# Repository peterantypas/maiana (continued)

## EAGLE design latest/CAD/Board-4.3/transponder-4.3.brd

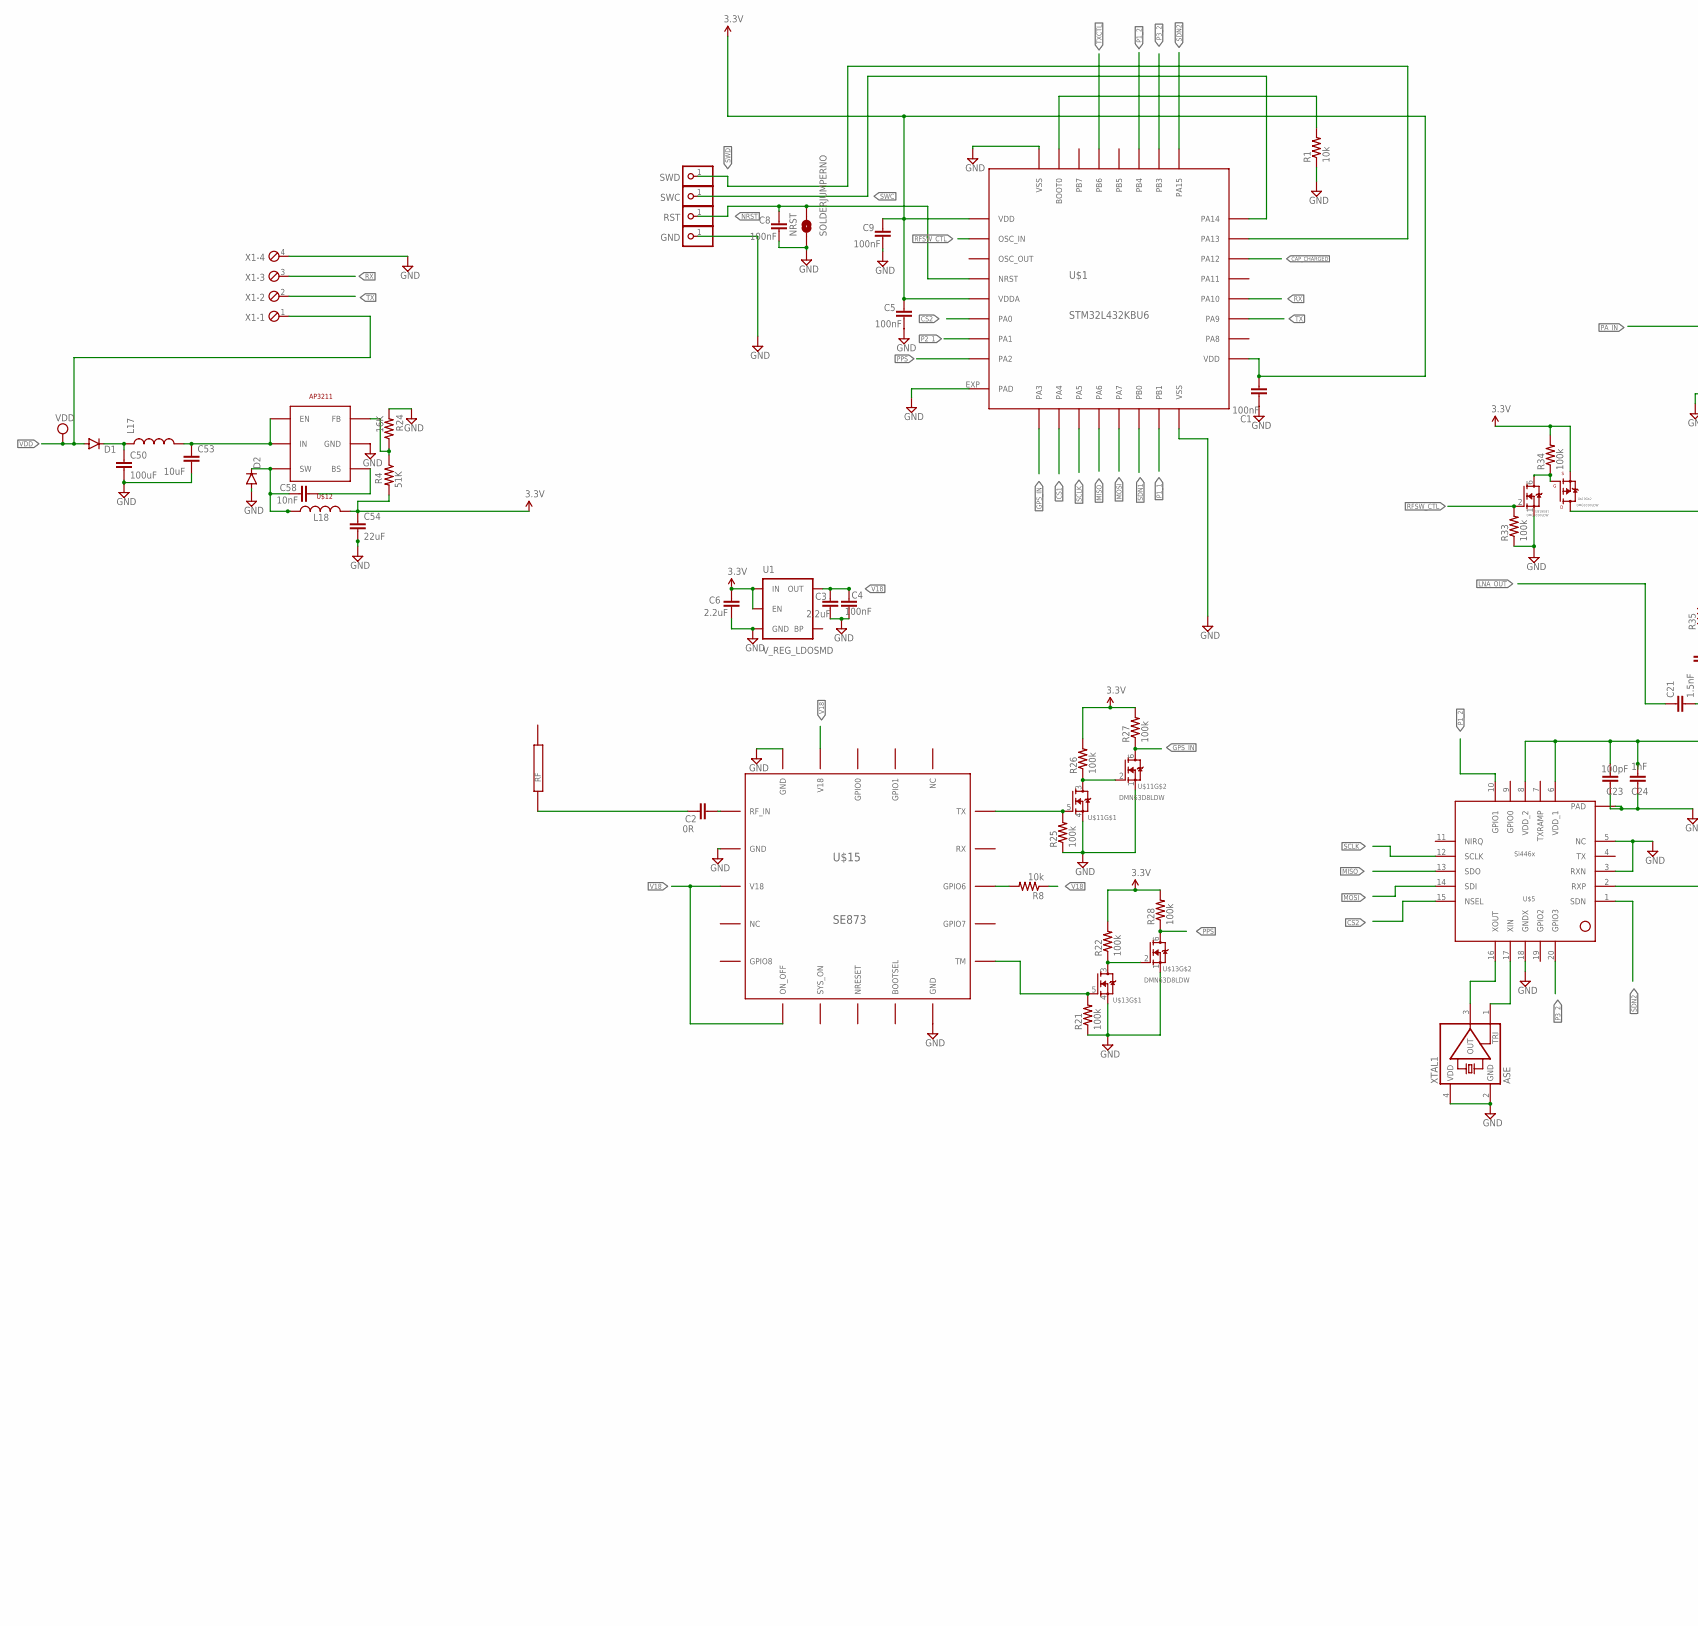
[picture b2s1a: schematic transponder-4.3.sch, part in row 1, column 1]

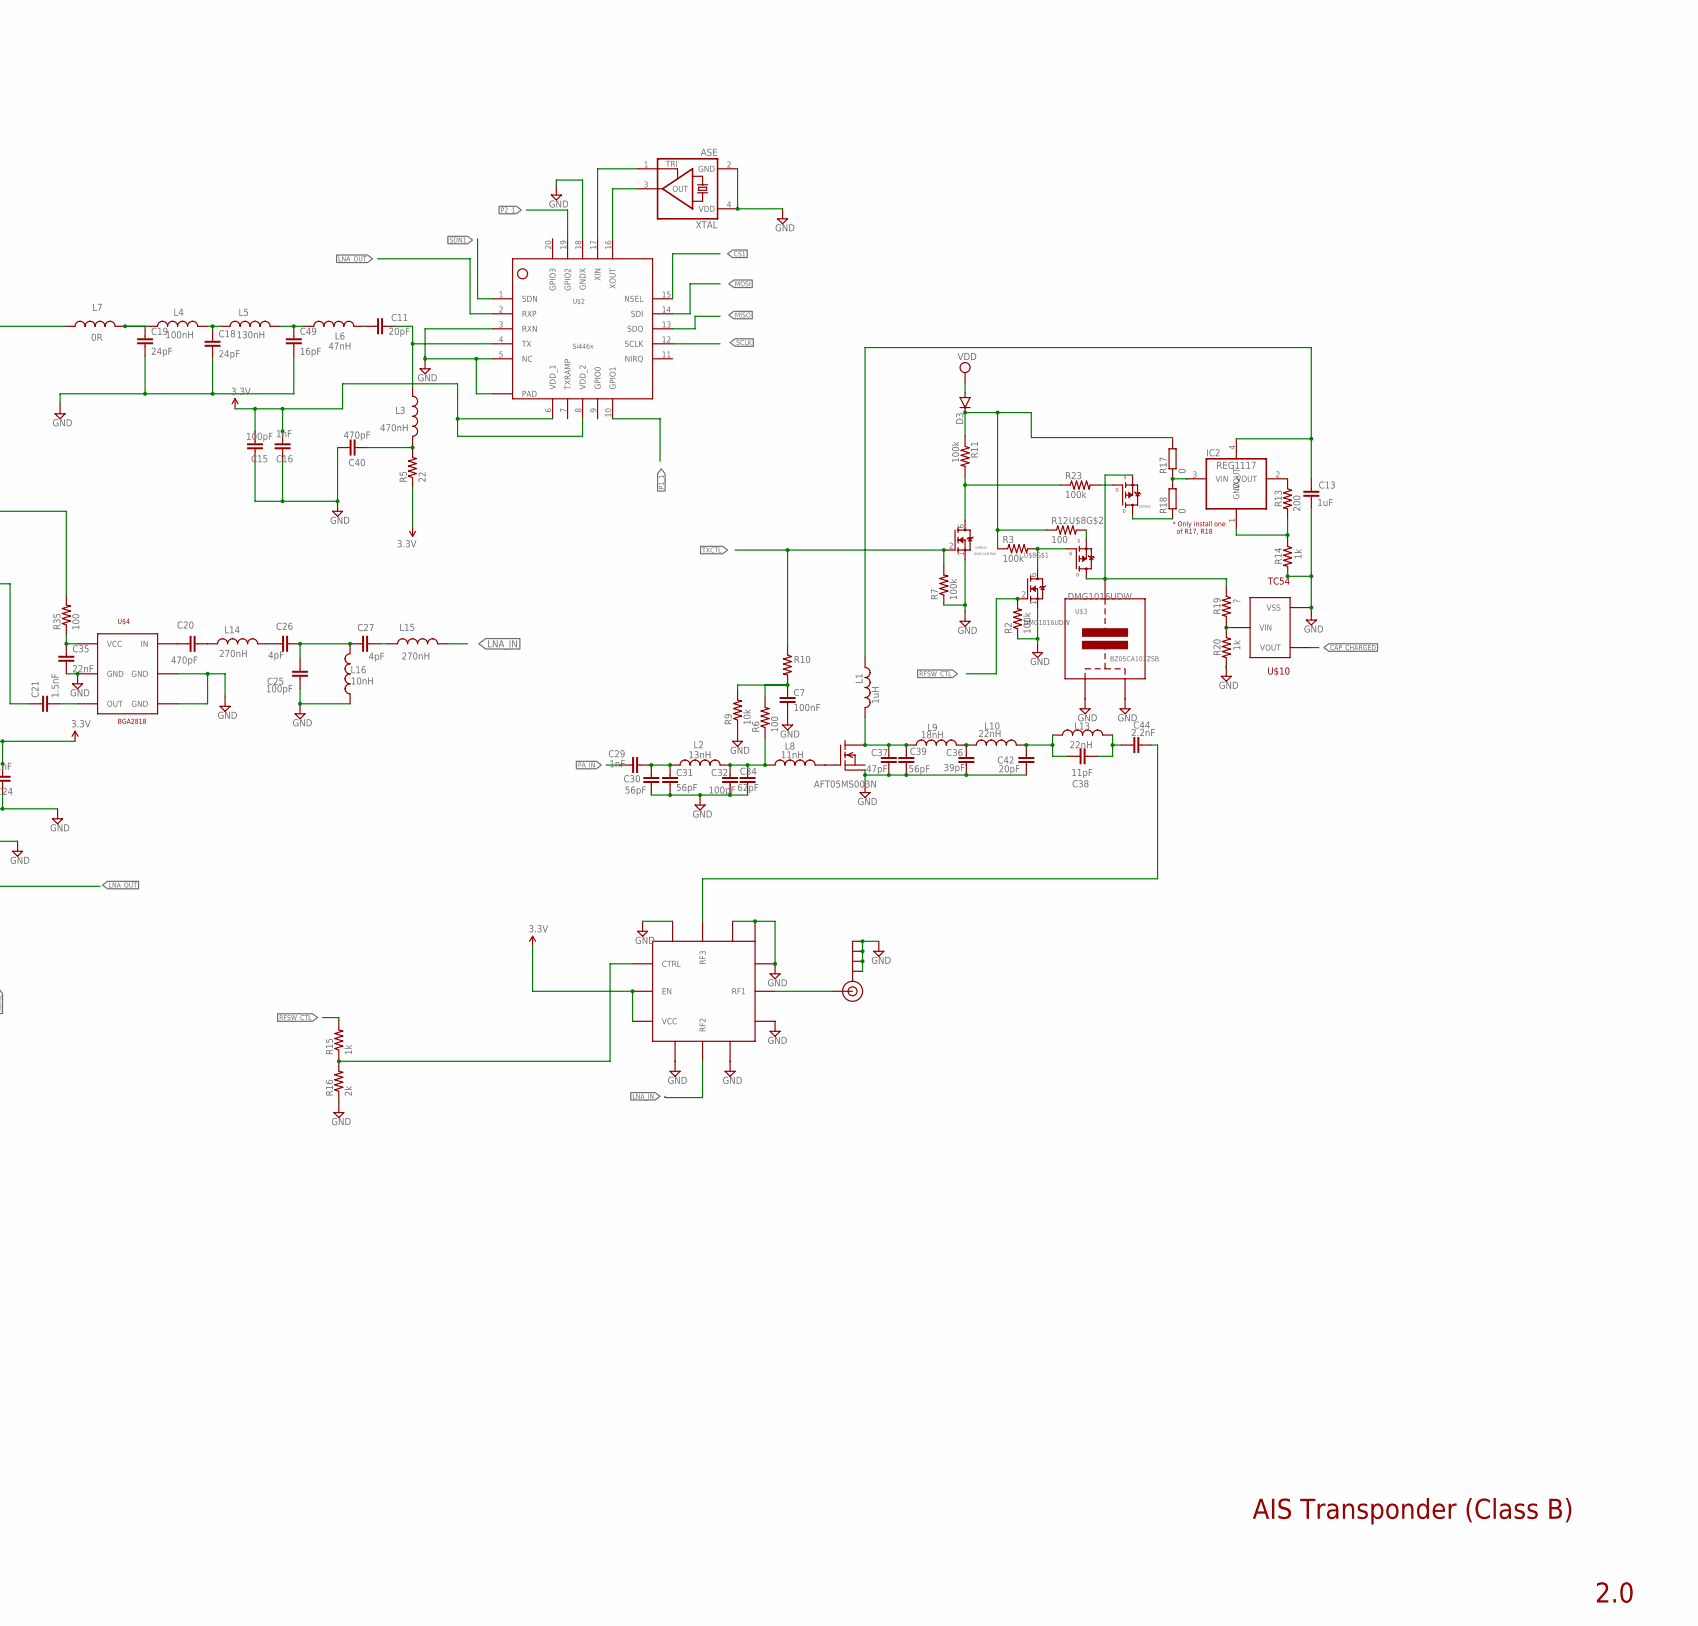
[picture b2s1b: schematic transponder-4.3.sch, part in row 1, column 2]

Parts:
C1, C4, C5, C7, C8, C9: 100nF; 0603-CAP
C2: 0R; 0603-CAP
C3, C6: 2.2uF; 0603-CAP
C11: 20pF; 0603-CAP
C13: 1uF; 0603-CAP
C15, C23, C25, C32: 100pF; 0603-CAP
C16, C24, C29: 1nF; 0603-CAP
C18, C19: 24pF; 0603-CAP
C20, C40: 470pF; 0603-CAP
C21: 1.5nF; 0603-CAP
C26, C27: 4pF; 0603-CAP
C30, C31: 56pF; 0603-CAP
C34: 62pF; 0603-CAP
C35: 22nF; 0603-CAP
C36: 39pF; 0805
C37: 47pF; 0805
C38: 11pF; 0805
C39: 56pF; 0805
C42: 20pF; 0805
C44: 2.2nF; 0805
C49: 16pF; 0603-CAP
C50: 100uF; 1210
C53: 10uF; 0805
C54: 22uF; 0805
C58: 10nF; 0603-CAP
D1, D2, D3: DIODESOD123; SOD-123
GND: PINHD-1X1; 1X01
IC2: REG1117; SOT223
J$1: SMA_EDGE; SMA-EDGE
L1: 1uH; 0805
L2: 13nH; 0603
L3: 470nH; 0603
L4: 100nH; 0603
L5: 130nH; 0603
L6: 47nH; 0603
L7: 0R; 0603
L8: 11nH; 0603
L9: 18nH; 0805
L10, L13: 22nH; 0805
L14, L15: 270nH; 0603
L16: 10nH; 0603
L17: INDUCTOR1007; 1007
L18: INDUCTOR0805; 0805
NRST: SOLDERJUMPERNO; SJ_2S-NO
R1, R8, R9: 10k; 0603-RES
R2, R3, R7, R11, R21, R22, R23, R25, R26, R27, R28, R33, R34: 100k; 0603-RES
R4: 51K; 0603-RES
R5: 22; 0603-RES
R6, R12, R35: 100; 0603-RES
R10: RESISTOR0603-RES; 0603-RES
R13: 200; 0603-RES
R14, R15, R20: 1k; 0603-RES
R16: 2k; 0603-RES
R17, R18: 0; R0603
R19: ?; 0603-RES
R24: 16K; 0603-RES
RST: PINHD-1X1; 1X01
SWC: PINHD-1X1; 1X01
SWD: PINHD-1X1; 1X01
U1: V_REG_LDOSMD; SOT23-5
U$1: STM32L432KBU6; QFN32
U$2, U$5: SI4463
U$3: BZ05CA103ZSB; BZ05
U$4: BGA2818; SOT363
U$6: SKYWORKS-13330397LF; QFN12
U$7: AFT05MS003N; SOT-89
U$8, U$9, U$19: DMG1016UDW; SOT363
U$10: TC54; SOT23
U$11, U$13: DMN63D8LDW; SOT363
U$12: AP3211; SOT23-6
U$14: 1575AT43A0040E
U$15: SE873
X1: MPT4; 4POL254
XTAL, XTAL1: ASE

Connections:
3.3V: C1.2, C5.2, C6.2, C9.2, C15.1, C16.1, C23.1, C24.1, C54.1, L18.2, R4.2, R5.1, R22.2, R26.2, R27.2, R28.2, R34.2, U1.1 (IN), U1.3 (EN), U$1.1 (VDD), U$1.5 (VDDA), U$1.17 (VDD), U$2.6 (VDD_1), U$2.8 (VDD_2), U$5.6 (VDD_1), U$5.8 (VDD_2), U$6.P$8 (EN), U$6.P$9 (VCC), U$19.4 (S)
CAP_CHARGED: U$1.22 (PA12), U$10.1 (VOUT)
CS1: U$1.10 (PA4), U$2.15 (NSEL)
CS2: U$1.6 (PA0), U$5.15 (NSEL)
GND: C1.1, C3.1, C4.1, C5.1, C6.1, C7.2, C8.1, C9.1, C13.2, C15.2, C16.2, C18.2, C19.2, C23.2, C24.2, C25.1, C30.2, C31.2, C32.2, C34.2, C35.2, C36.2, C37.2, C39.2, C40.2, C42.2, C49.2, C50.2, C53.2, C54.2, D2.A, GND.1, J$1.GND@0 (GND), J$1.GND@1 (GND), J$1.GND@2 (GND), J$1.GND@3 (GND), L16.1, NRST.1, R1.1, R2.1, R7.1, R9.1, R14.2, R16.1, R20.2, R21.1, R24.2, R25.1, R33.1, U1.2 (GND), U$1.16 (VSS), U$1.32 (VSS), U$1.EXP (PAD), U$2.3 (RXN), U$2.5 (NC), U$2.18 (GNDX), U$2.EXP (PAD), U$3.P$1, U$3.P$2, U$4.2 (GND), U$4.4 (GND), U$4.5 (GND), U$5.3 (RXN), U$5.5 (NC), U$5.18 (GNDX), U$5.EXP (PAD), U$6.P$1 (GND), U$6.P$3 (GND), U$6.P$4 (GND), U$6.P$6 (GND), U$6.P$10 (GND), U$6.P$12 (GND), U$7.2@1 (PAD), U$8.1 (S), U$9.1 (S), U$10.2 (VSS), U$11.1 (S), U$11.4 (S), U$12.2 (GND), U$13.1 (S), U$13.4 (S), U$15.P$2 (GND), U$15.P$10 (GND), U$15.P$20 (GND), U$19.1 (S), X1.4, XTAL.2 (GND), XTAL.4 (VDD), XTAL1.2 (GND), XTAL1.4 (VDD)
GNSS_RF: C2.2, U$14.P$1 (RF)
GPS_IN: R27.1, U$1.9 (PA3), U$11.6 (D)
LNAPWR: C35.1, R35.1, U$4.1 (VCC)
LNAPWR1: R35.2, U$19.3 (D)
LNA_IN: L15.2, U$6.P$11 (RF2)
LNA_OUT: C21.1, U$2.2 (RXP), U$5.2 (RXP)
MISO: U$1.12 (PA6), U$2.13 (SDO), U$5.13 (SDO)
MOSI: U$1.13 (PA7), U$2.14 (SDI), U$5.14 (SDI)
unnamed: U$2.17 (XIN), XTAL.1 (TRI)
unnamed: C19.1, L4.1, L7.2
unnamed: C18.1, L4.2, L5.1
unnamed: R1.2, U$1.31 (BOOT0)
unnamed: R19.1, U$3.P$3, U$8.3 (D), U$9.4 (S)
unnamed: R21.2, U$13.5 (G), U$15.P$11 (TM)
unnamed: R11.2, R23.1, U$9.6 (D)
unnamed: C11.1, L3.1, U$2.4 (TX)
unnamed: R22.1, U$13.2 (G), U$13.3 (D)
unnamed: C20.1, U$4.6 (IN)
unnamed: C21.2, U$4.3 (OUT)
unnamed: R25.2, U$11.5 (G), U$15.P$15 (TX)
unnamed: U$2.16 (XOUT), XTAL.3 (OUT)
unnamed: R26.1, U$11.2 (G), U$11.3 (D)
unnamed: C20.2, L14.1
unnamed: R23.2, U$9.5 (G)
unnamed: C53.1, L17.2, U$12.4 (EN), U$12.5 (IN)
unnamed: C49.1, L5.2, L6.1
unnamed: R34.1, U$19.5 (G), U$19.6 (D)
unnamed: C37.1, C39.1, L1.2, L9.1, U$7.3 (D)
unnamed: L8.2, U$7.1 (G)
unnamed: C32.1, C34.1, L2.2, L8.1, R6.1
unnamed: C29.2, C30.1, C31.1, L2.1
unnamed: C36.1, L9.2, L10.1
unnamed: C38.1, C42.1, L10.2, L13.1
unnamed: R8.2, U$15.P$13 (GPIO6)
unnamed: IC2.3 (VIN), R17.1, R18.2
unnamed: IC2.2 (VOUT), R13.1
unnamed: C2.1, U$15.P$1 (RF_IN)
unnamed: C25.2, C26.1, C27.2, L16.2
unnamed: C27.1, L15.1
unnamed: C26.2, L14.2
unnamed: R18.1, U$9.3 (D)
unnamed: U$5.17 (XIN), XTAL1.1 (TRI)
unnamed: U$5.16 (XOUT), XTAL1.3 (OUT)
unnamed: R3.2, U$8.5 (G), U$8.6 (D)
unnamed: R12.2, U$8.4 (S)
unnamed: R19.2, R20.1, U$10.3 (VIN)
unnamed: C38.2, C44.1, L13.2
unnamed: J$1.SIG (SIGNAL), U$6.P$2 (RF1)
unnamed: C50.1, D1.C, L17.1
unnamed: IC2.1 (GND), R13.2, R14.1
unnamed: D3.C, R3.1, R11.1, R12.1, R17.2
unnamed: C11.2, L6.2
unnamed: C40.1, L3.2, R5.2
unnamed: C58.2, U$12.1 (BS)
unnamed: C58.1, D2.C, L18.1, U$12.6 (SW)
unnamed: R4.1, R24.1, U$12.3 (FB)
unnamed: C7.1, R6.2, R9.2, R10.2
NRST: C8.2, NRST.2, RST.1, U$1.4 (NRST)
P1_1: U$1.15 (PB1), U$2.10 (GPIO1)
P1_2: U$1.27 (PB4), U$5.10 (GPIO1)
P2_1: U$1.7 (PA1), U$2.19 (GPIO2)
P3_2: U$1.26 (PB3), U$5.20 (GPIO3)
PA_IN: C29.1, L7.1
PA_OUT: C44.2, U$6.P$5 (RF3)
PA_PWR: C13.1, IC2.4 (VOUT), L1.1
PPS: R28.1, U$1.8 (PA2), U$13.6 (D)
RFSWCTL: R15.1, R16.2, U$6.P$7 (CTRL)
RFSW_CTL: R2.2, R15.2, R33.2, U$1.2 (OSC_IN), U$8.2 (G), U$19.2 (G)
RX: U$1.20 (PA10), X1.3
SCLK: U$1.11 (PA5), U$2.12 (SCLK), U$5.12 (SCLK)
SDN1: U$1.14 (PB0), U$2.1 (SDN)
SDN2: U$1.25 (PA15), U$5.1 (SDN)
SWC: SWC.1, U$1.24 (PA14)
SWD: SWD.1, U$1.23 (PA13)
TX: U$1.19 (PA9), X1.2
TXCTL: R7.2, R10.1, U$1.29 (PB6), U$9.2 (G)
V18: C3.2, C4.2, R8.1, U1.5 (OUT), U$15.P$3 (V18), U$15.P$6 (ON_OFF), U$15.P$19 (V18)
VDD: D1.A, D3.A, X1.1

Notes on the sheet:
AIS Transponder (Class B)
2.0
* Only install one of R17, R18

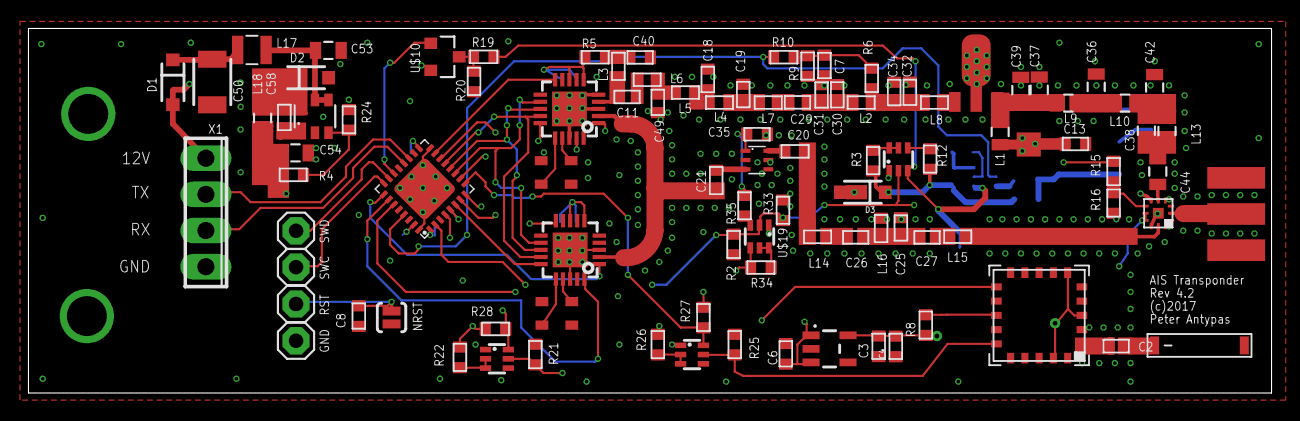
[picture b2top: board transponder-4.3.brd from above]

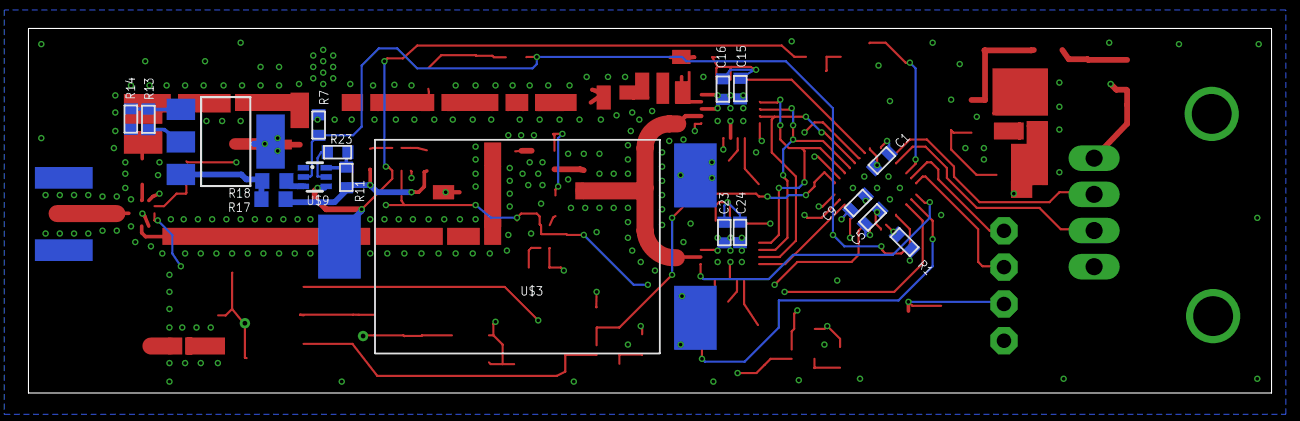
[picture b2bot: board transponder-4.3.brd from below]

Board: 4 copper layers, 87.3 x 25.6 mm, 117 parts (18 on the bottom side), 83 nets.

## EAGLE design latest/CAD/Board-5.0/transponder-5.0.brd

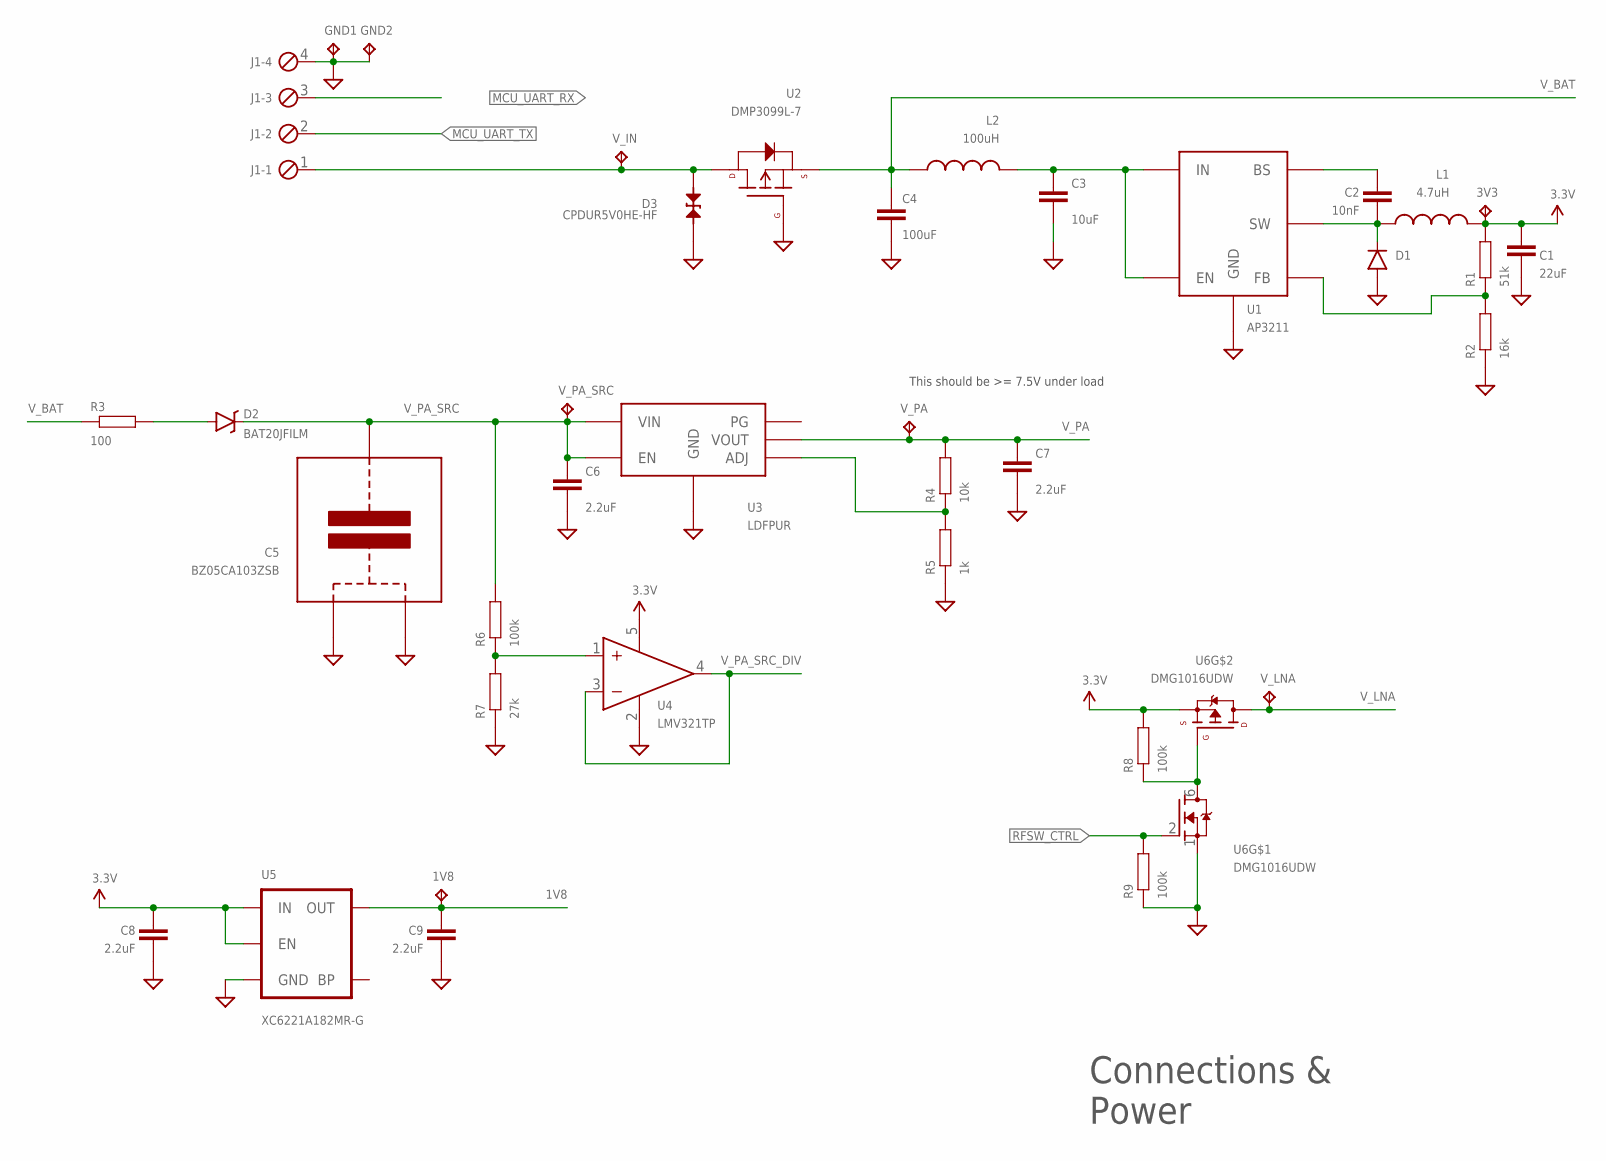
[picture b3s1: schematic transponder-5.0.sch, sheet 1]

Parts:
1V8, 3V3: TPTP12R; TP12R
C1: 22uF; 0805
C2: 10nF; 0603-CAP
C3: 10uF; 0805
C4: 100uF; 1210
C5: BZ05CA103ZSB; BZ05
C6, C7, C8, C9: 2.2uF; 0603-CAP
D1: DIODESOD123; SOD-123
D2: BAT20JFILM; SOD-323
D3: CPDUR5V0HE-HF; 0603
GND1, GND2: TPTP12R; TP12R
J1: MPT4; 4POL254
L1: 4.7uH; 0805
L2: 100uH; 1007
R1: 51k; 0603-RES
R2: 16k; 0603-RES
R3: 100; 0603-RES
R4: 10k; 0603-RES
R5: 1k; 0603-RES
R6, R8, R9: 100k; 0603-RES
R7: 27k; 0603-RES
U1: AP3211; SOT23-6
U2: DMP3099L-7; SOT23-3
U3: LDFPUR; DFN-6
U4: LMV321TP; SOT23-5
U5: XC6221A182MR-G; SOT23-5
U6: DMG1016UDW; SOT363
V_IN: TPTP12R; TP12R
V_LNA: TPTP12R; TP12R
V_PA: TPTP12R; TP12R
V_PA_SRC: TPTP12R; TP12R

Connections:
1V8: 1V8.TP, C9.1, U5.5 (OUT); also elsewhere on the board
3.3V: 3V3.TP, C1.1, C8.1, L1.2, R1.2, R8.2, U4.5 (V+), U5.1 (IN), U5.3 (EN), U6.4 (S); also elsewhere on the board
GND: C1.2, C3.2, C4.2, C5.P$1, C5.P$2, C6.2, C7.2, C8.2, C9.2, D1.A, D3.2, GND1.TP, GND2.TP, J1.4, R2.1, R5.1, R7.1, R9.1, U1.2 (GND), U2.1 (G), U3.P$4 (GND), U3.P$7 (GND), U4.2 (V-), U5.2 (GND), U6.1 (S); also elsewhere on the board
MCU_UART_RX: J1.3; also elsewhere on the board
MCU_UART_TX: J1.2; also elsewhere on the board
unnamed: C3.1, L2.2, U1.4 (EN), U1.5 (IN)
unnamed: C2.2, D1.C, L1.1, U1.6 (SW)
unnamed: D2.A, R3.2
unnamed: C2.1, U1.1 (BS)
unnamed: R1.1, R2.2, U1.3 (FB)
unnamed: R8.1, U6.5 (G), U6.6 (D)
unnamed: R6.1, R7.2, U4.1 (IN+)
unnamed: R4.1, R5.2, U3.P$2 (ADJ)
RFSW_CTRL: R9.2, U6.2 (G); also elsewhere on the board
V_BAT: C4.1, L2.1, R3.1, U2.2 (S)
V_IN: D3.1, J1.1, U2.3 (D), V_IN.TP
V_LNA: U6.3 (D), V_LNA.TP; also elsewhere on the board
V_PA: C7.1, R4.2, U3.P$1 (VOUT), V_PA.TP; also elsewhere on the board
V_PA_SRC: C5.P$3, C6.1, D2.C, R6.2, U3.P$5 (EN), U3.P$6 (VIN), V_PA_SRC.TP
V_PA_SRC_DIV: U4.3 (IN-), U4.4 (OUT); also elsewhere on the board

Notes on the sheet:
Connections & Power
This should be >= 7.5V under load

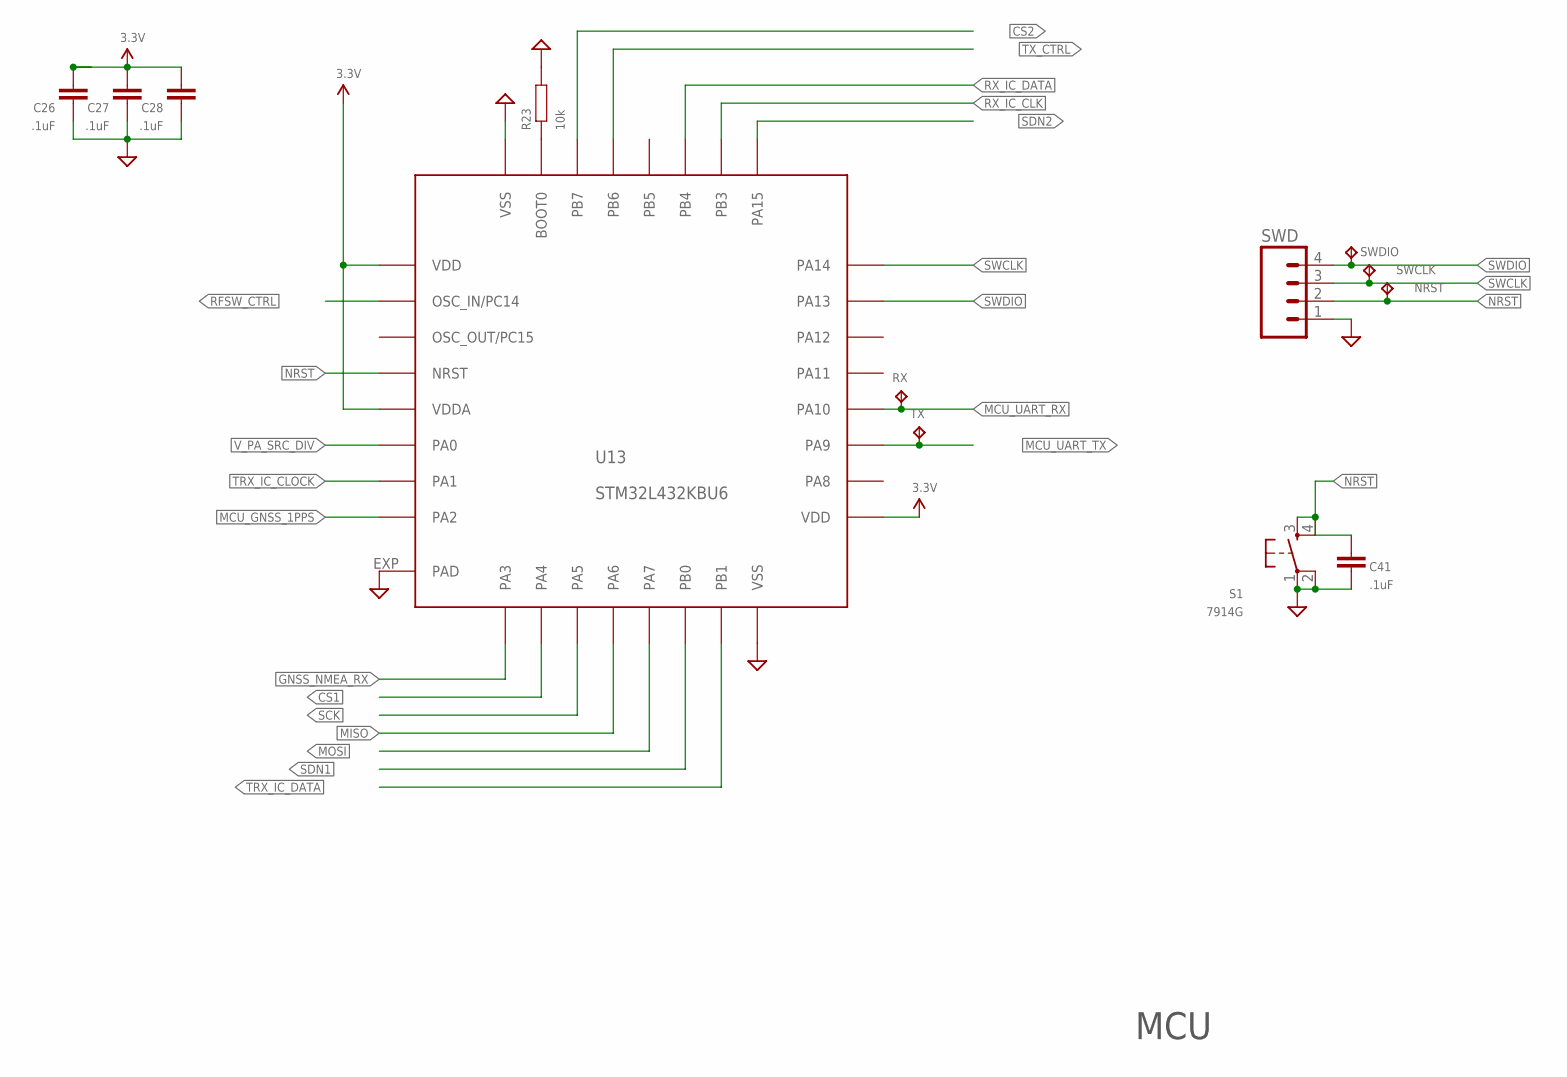
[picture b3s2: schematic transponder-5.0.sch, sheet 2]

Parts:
C26, C27, C28, C41: .1uF; 0603-CAP
NRST: TPTP12R; TP12R
R23: 10k; 0603-RES
RX: TPTP12R; TP12R
S1: 7914G
SWCLK: TPTP12R; TP12R
SWD: M04PTH; 1X04
SWDIO: TPTP12R; TP12R
TX: TPTP12R; TP12R
U13: STM32L432KBU6; QFN32

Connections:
3.3V: C26.1, C27.1, C28.1, U13.1 (VDD), U13.5 (VDDA), U13.17 (VDD); also elsewhere on the board
CS1: U13.10 (PA4); also elsewhere on the board
CS2: U13.30 (PB7); also elsewhere on the board
GND: C26.2, C27.2, C28.2, C41.2, R23.2, S1.1, S1.2, SWD.1, U13.16 (VSS), U13.32 (VSS), U13.EXP (PAD); also elsewhere on the board
GNSS_NMEA_RX: U13.9 (PA3); also elsewhere on the board
MCU_GNSS_1PPS: U13.8 (PA2); also elsewhere on the board
MCU_UART_RX: RX.TP, U13.20 (PA10); also elsewhere on the board
MCU_UART_TX: TX.TP, U13.19 (PA9); also elsewhere on the board
MISO: U13.12 (PA6); also elsewhere on the board
MOSI: U13.13 (PA7); also elsewhere on the board
unnamed: R23.1, U13.31 (BOOT0)
NRST: C41.1, NRST.TP, S1.3, S1.4, SWD.2, U13.4 (NRST)
RFSW_CTRL: U13.2 (OSC_IN/PC14); also elsewhere on the board
RX_IC_CLK: U13.26 (PB3); also elsewhere on the board
RX_IC_DATA: U13.27 (PB4); also elsewhere on the board
SCK: U13.11 (PA5); also elsewhere on the board
SDN1: U13.14 (PB0); also elsewhere on the board
SDN2: U13.25 (PA15); also elsewhere on the board
SWCLK: SWCLK.TP, SWD.3, U13.24 (PA14)
SWDIO: SWD.4, SWDIO.TP, U13.23 (PA13)
TRX_IC_CLOCK: U13.7 (PA1); also elsewhere on the board
TRX_IC_DATA: U13.15 (PB1); also elsewhere on the board
TX_CTRL: U13.29 (PB6); also elsewhere on the board
V_PA_SRC_DIV: U13.6 (PA0); also elsewhere on the board

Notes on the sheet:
MCU

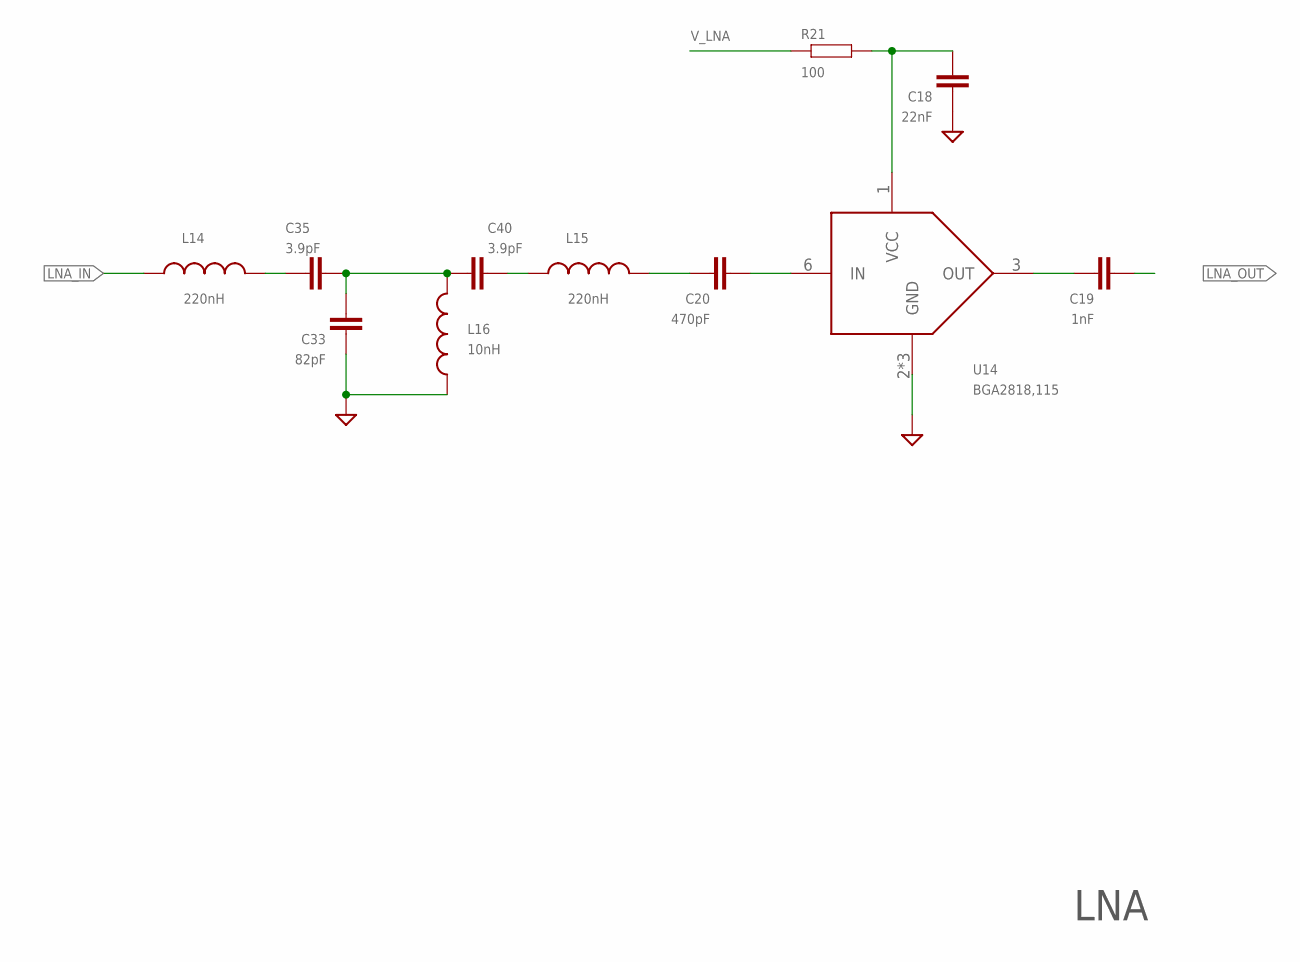
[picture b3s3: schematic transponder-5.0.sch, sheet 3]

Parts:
C18: 22nF; 0603-CAP
C19: 1nF; 0603-CAP
C20: 470pF; 0603-CAP
C33: 82pF; 0603-CAP
C35, C40: 3.9pF; 0603-CAP
L14, L15: 220nH; 0603
L16: 10nH; 0603
R21: 100; 0603-RES
U14: BGA2818,115; SOT363

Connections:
GND: C18.2, C33.1, L16.1, U14.2 (GND), U14.4 (GND), U14.5 (GND); also elsewhere on the board
LNA_IN: L14.1; also elsewhere on the board
LNA_OUT: C19.2; also elsewhere on the board
unnamed: C20.2, U14.6 (IN)
unnamed: C18.1, R21.2, U14.1 (VCC)
unnamed: C33.2, C35.1, C40.2, L16.2
unnamed: C40.1, L15.1
unnamed: C35.2, L14.2
unnamed: C20.1, L15.2
unnamed: C19.1, U14.3 (OUT)
V_LNA: R21.1; also elsewhere on the board

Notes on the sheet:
LNA

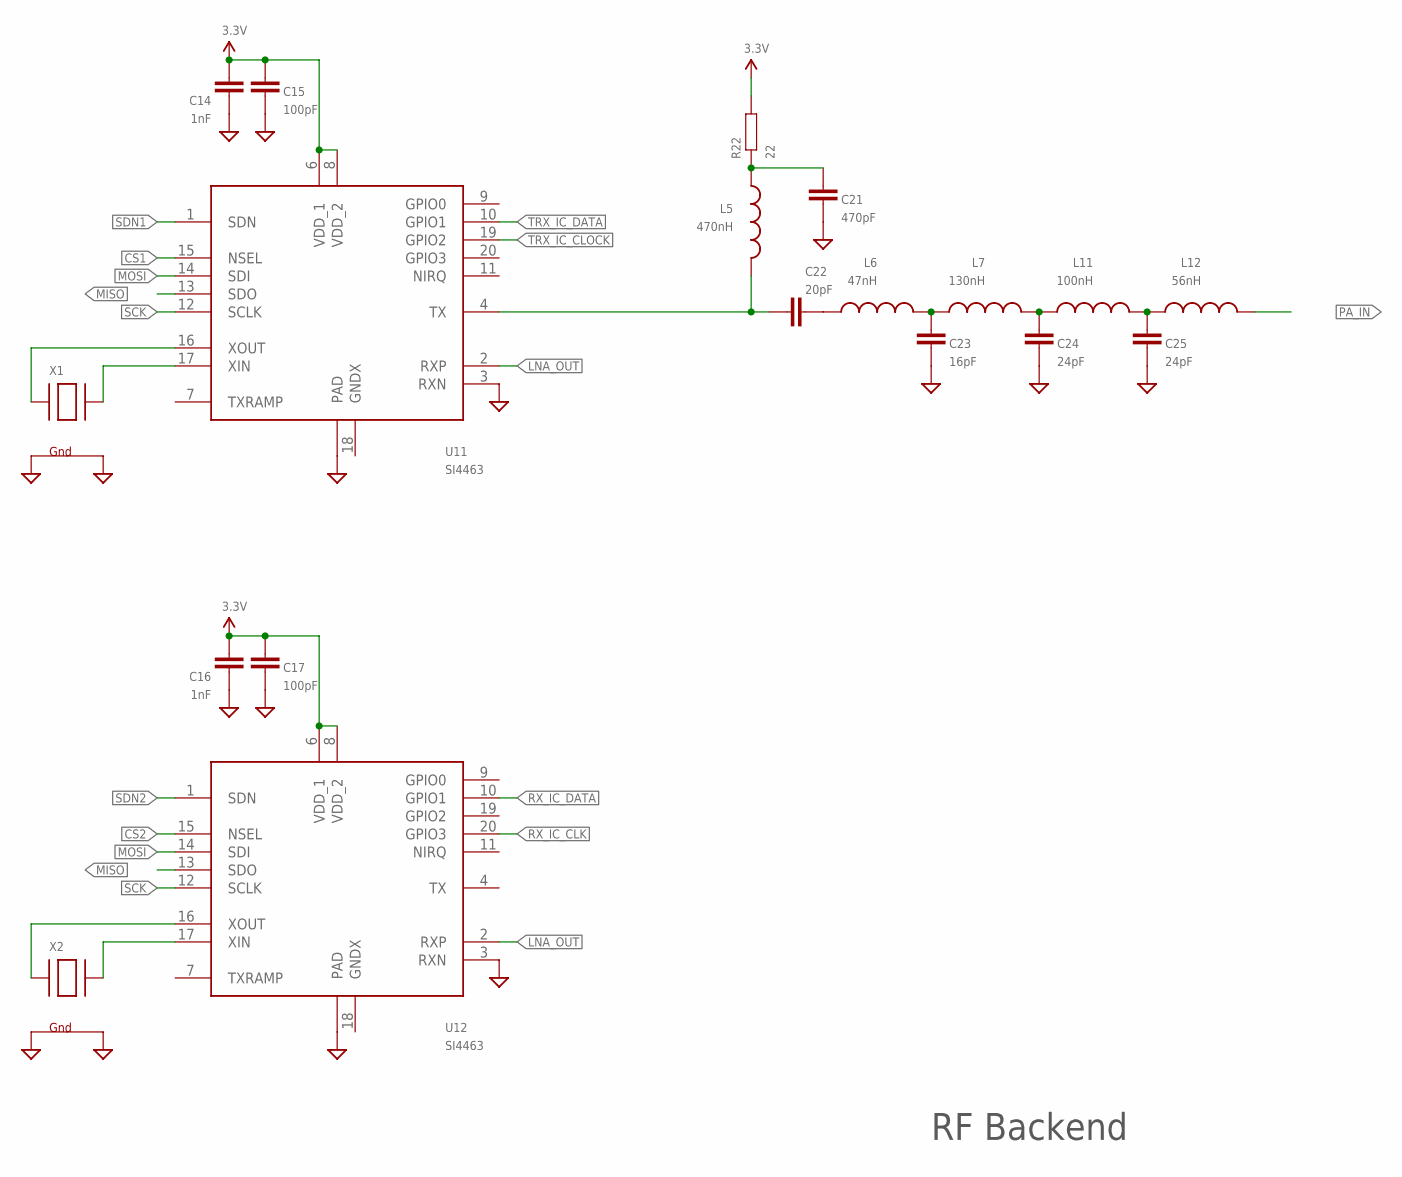
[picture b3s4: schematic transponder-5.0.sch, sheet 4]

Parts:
C14, C16: 1nF; 0603-CAP
C15, C17: 100pF; 0603-CAP
C21: 470pF; 0603-CAP
C22: 20pF; 0603-CAP
C23: 16pF; 0603-CAP
C24, C25: 24pF; 0603-CAP
L5: 470nH; 0603
L6: 47nH; 0603
L7: 130nH; 0603
L11: 100nH; 0603
L12: 56nH; 0603
R22: 22; 0603-RES
U11, U12: SI4463
X1, X2: XTAL-4-3225; NX3225

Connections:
3.3V: C14.1, C15.1, C16.1, C17.1, R22.2, U11.6 (VDD_1), U11.8 (VDD_2), U12.6 (VDD_1), U12.8 (VDD_2); also elsewhere on the board
CS1: U11.15 (NSEL); also elsewhere on the board
CS2: U12.15 (NSEL); also elsewhere on the board
GND: C14.2, C15.2, C16.2, C17.2, C21.2, C23.2, C24.2, C25.2, U11.3 (RXN), U11.EXP (PAD), U12.3 (RXN), U12.EXP (PAD), X1.2 (G2), X1.4 (G1), X2.2 (G2), X2.4 (G1); also elsewhere on the board
LNA_OUT: U11.2 (RXP), U12.2 (RXP); also elsewhere on the board
MISO: U11.13 (SDO), U12.13 (SDO); also elsewhere on the board
MOSI: U11.14 (SDI), U12.14 (SDI); also elsewhere on the board
unnamed: U12.16 (XOUT), X2.1 (X1)
unnamed: U12.17 (XIN), X2.3 (X2)
unnamed: U11.16 (XOUT), X1.1 (X1)
unnamed: U11.17 (XIN), X1.3 (X2)
unnamed: C22.1, L5.2, U11.4 (TX)
unnamed: C21.1, L5.1, R22.1
unnamed: C22.2, L6.1
unnamed: C23.1, L6.2, L7.1
unnamed: C24.1, L7.2, L11.1
unnamed: C25.1, L11.2, L12.1
PA_IN: L12.2; also elsewhere on the board
RX_IC_CLK: U12.20 (GPIO3); also elsewhere on the board
RX_IC_DATA: U12.10 (GPIO1); also elsewhere on the board
SCK: U11.12 (SCLK), U12.12 (SCLK); also elsewhere on the board
SDN1: U11.1 (SDN); also elsewhere on the board
SDN2: U12.1 (SDN); also elsewhere on the board
TRX_IC_CLOCK: U11.19 (GPIO2); also elsewhere on the board
TRX_IC_DATA: U11.10 (GPIO1); also elsewhere on the board

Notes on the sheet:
RF Backend

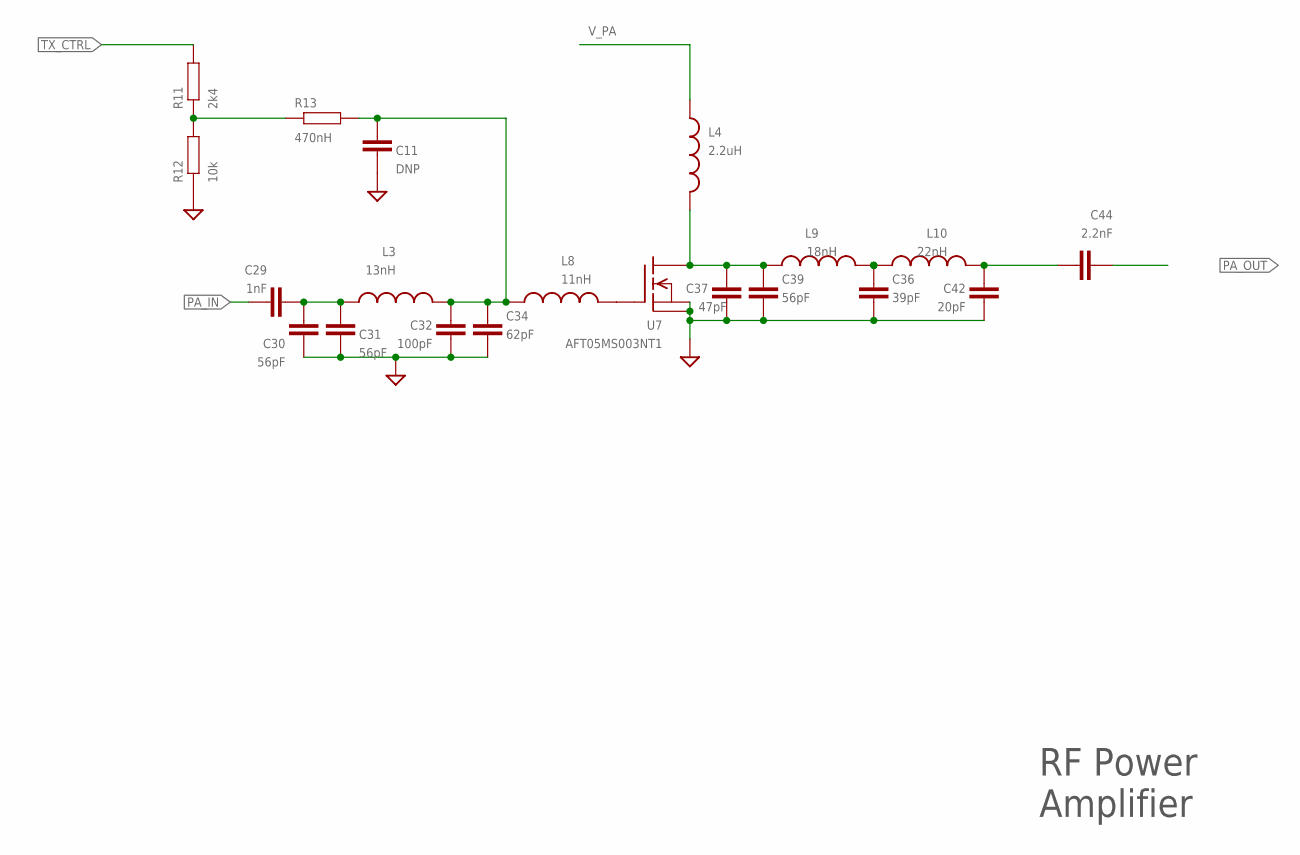
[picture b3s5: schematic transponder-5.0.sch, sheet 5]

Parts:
C11: DNP; 0603-CAP
C29: 1nF; 0603-CAP
C30, C31: 56pF; 0603-CAP
C32: 100pF; 0603-CAP
C34: 62pF; 0603-CAP
C36: 39pF; 0805
C37: 47pF; 0805
C39: 56pF; 0805
C42: 20pF; 0805
C44: 2.2nF; 0805
L3: 13nH; 0603
L4: 2.2uH; 0805
L8: 11nH; 0603
L9: 18nH; 0805
L10: 22nH; 0805
R11: 2k4; 0603-RES
R12: 10k; 0603-RES
R13: 470nH; 0603-RES
U7: AFT05MS003NT1; SOT-89

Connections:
GND: C11.2, C30.2, C31.2, C32.2, C34.2, C36.2, C37.2, C39.2, C42.2, R12.1, U7.2 (S), U7.2@1 (PAD); also elsewhere on the board
unnamed: R11.1, R12.2, R13.1
unnamed: C37.1, C39.1, L4.2, L9.1, U7.3 (D)
unnamed: L8.2, U7.1 (G)
unnamed: C11.1, C32.1, C34.1, L3.2, L8.1, R13.2
unnamed: C29.2, C30.1, C31.1, L3.1
unnamed: C36.1, L9.2, L10.1
unnamed: C42.1, C44.1, L10.2
PA_IN: C29.1; also elsewhere on the board
PA_OUT: C44.2; also elsewhere on the board
TX_CTRL: R11.2; also elsewhere on the board
V_PA: L4.1; also elsewhere on the board

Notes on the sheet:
RF Power Amplifier
